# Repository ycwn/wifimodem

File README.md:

# wifimodem
ESP32 Wireless modem, compatible with PC XT/AT, C64, and Amiga

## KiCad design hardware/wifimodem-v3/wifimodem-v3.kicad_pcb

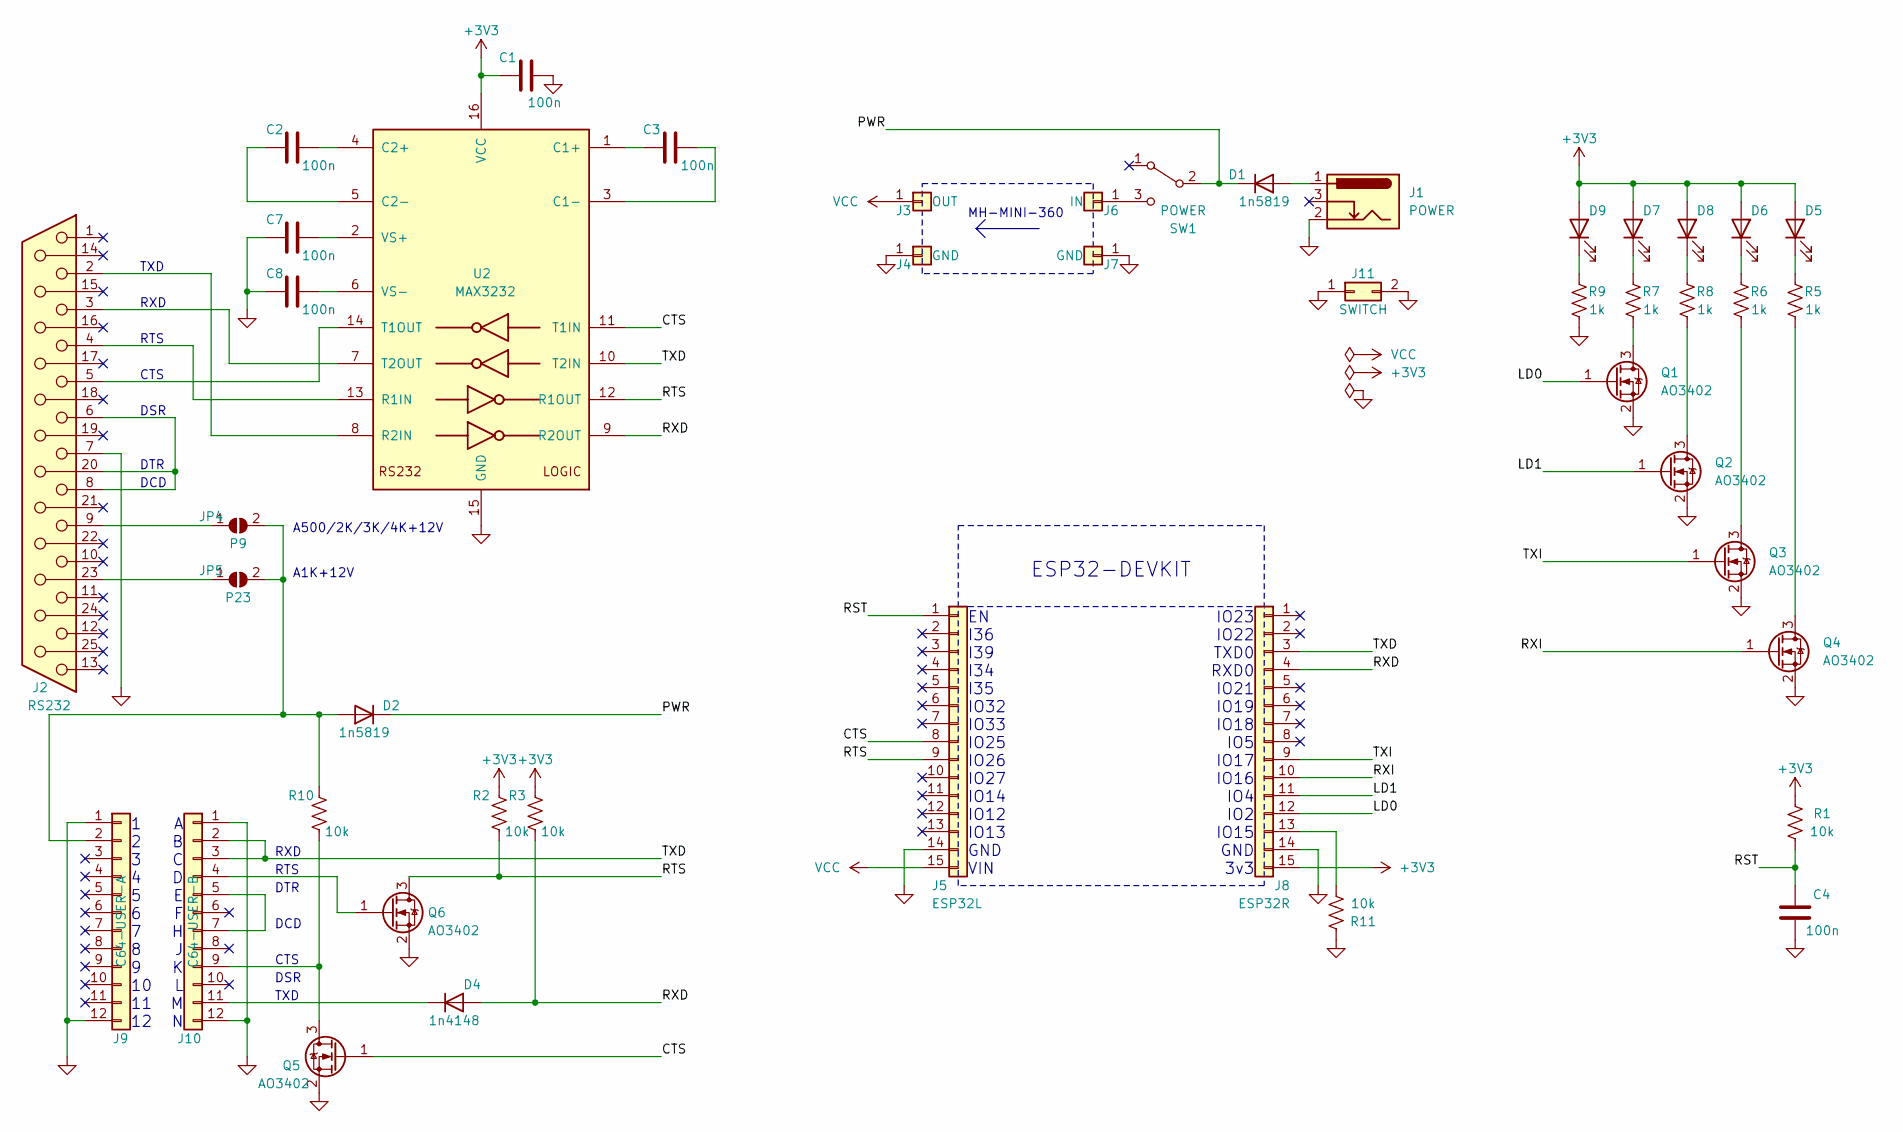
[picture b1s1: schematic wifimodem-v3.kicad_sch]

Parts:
C1, C2, C3, C4, C7, C8: 100n; C_0805_2012Metric
D1, D2: 1n5819; D_DO-34_SOD68_P2.54mm_Vertical_KathodeUp
D4: 1n4148; D_1206_3216Metric
D5: RXD; LED_D3.0mm
D6: TXD; LED_D3.0mm
D7: APS; LED_D3.0mm
D8: CON; LED_D3.0mm
D9: PWR; LED_D3.0mm
J1: POWER; BarrelJack_Horizontal
J2: RS232; DSUB-25_Female_Horizontal_P2.77x2.84mm_EdgePinOffset7.70mm_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
J3: OUT; TestPoint_Pad_2.0x2.0mm
J4, J7: GND; TestPoint_Pad_2.0x2.0mm
J5: ESP32L; PinSocket_1x15_P2.54mm_Vertical
J6: IN; TestPoint_Pad_2.0x2.0mm
J8: ESP32R; PinSocket_1x15_P2.54mm_Vertical
J9: C64-USER-A; Molex_KK-396_5273-12A_1x12_P3.96mm_Vertical
J10: C64-USER-B; Molex_KK-396_5273-12A_1x12_P3.96mm_Vertical
J11: SWITCH; PinSocket_2x01_P2.54mm_Horizontal
JP4: P9; SolderJumper-2_P1.3mm_Open_Pad1.0x1.5mm
JP5: P23; SolderJumper-2_P1.3mm_Open_Pad1.0x1.5mm
Q1, Q2, Q3, Q4, Q5, Q6: AO3402; SOT-23
R1, R2, R3, R10, R11: 10k; R_0805_2012Metric
R5, R6, R7, R8, R9: 1k; R_0805_2012Metric
SW1: POWER; PinSocket_1x03_P2.54mm_Vertical
U2: MAX3232; SOIC-16_3.9x9.9mm_P1.27mm

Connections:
+3V3: C1.1, D5.2 (A), D6.2 (A), D7.2 (A), D8.2 (A), D9.2 (A), J8.15, R1.2, R2.2, R3.2, U2.16 (VCC)
/CTS: J5.8, Q5.1 (G), U2.11 (T1IN)
/LD0: J8.12, Q1.1 (G)
/LD1: J8.11, Q2.1 (G)
/PWR: D1.1 (K), D2.1 (K), SW1.2 (B)
/RST: C4.1, J5.1, R1.1
/RTS: J5.9, Q6.3 (D), R2.1, U2.12 (R1OUT)
/RXD: D4.2 (A), J8.4, R3.1, U2.9 (R2OUT)
/RXI: J8.10, Q4.1 (G)
/TXD: J8.3, J10.2, J10.3, U2.10 (T2IN)
/TXI: J8.9, Q3.1 (G)
GND: C1.2, C4.2, C7.2, C8.2, J1.2, J2.7, J4.1, J5.14, J7.1, J8.14, J9.1, J9.12, J10.1, J10.12, J11.1, J11.2, Q1.2 (S), Q2.2 (S), Q3.2 (S), Q4.2 (S), Q5.2 (S), Q6.2 (S), R9.1, R11.2, U2.15 (GND)
unnamed: C2.1, U2.4 (C2+)
unnamed: C2.2, U2.5 (C2-)
unnamed: C3.1, U2.1 (C1+)
unnamed: C3.2, U2.3 (C1-)
unnamed: C7.1, U2.2 (VS+)
unnamed: C8.1, U2.6 (VS-)
unnamed: D1.2 (A), J1.1
unnamed: D2.2 (A), J9.2, JP4.2 (B), JP5.2 (B), R10.2
unnamed: D4.1 (K), J10.11
unnamed: D5.1 (K), R5.2
unnamed: D6.1 (K), R6.2
unnamed: D7.1 (K), R7.2
unnamed: D8.1 (K), R8.2
unnamed: D9.1 (K), R9.2
unnamed: J2.2, U2.8 (R2IN)
unnamed: J2.3, U2.7 (T2OUT)
unnamed: J2.4, U2.13 (R1IN)
unnamed: J2.5, U2.14 (T1OUT)
unnamed: J2.9, JP4.1 (A)
unnamed: J2.6, J2.8, J2.20
unnamed: J2.23, JP5.1 (A)
unnamed: J6.1, SW1.3 (C)
unnamed: J8.13, R11.1
unnamed: J10.4, Q6.1 (G)
unnamed: J10.5, J10.7
unnamed: J10.9, Q5.3 (D), R10.1
unnamed: Q1.3 (D), R7.1
unnamed: Q2.3 (D), R8.1
unnamed: Q3.3 (D), R6.1
unnamed: Q4.3 (D), R5.1
VCC: J3.1, J5.15

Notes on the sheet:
RTS
DTR
RXD
DCD
CTS
ESP32-DEVKIT
DSR
IO23 IO22 TXD0 RXD0 IO21 IO19 IO18 IO5 IO17 IO16 IO4 IO2 IO15 GND 3v3
A500/2K/3K/4K+12V
MH-MINI-360
A1K+12V
TXD
A B C D E F H J K L M N
1 2 3 4 5 6 7 8 9 10 11 12
EN I36 I39 I34 I35 IO32 IO33 IO25 IO26 IO27 IO14 IO12 IO13 GND VIN

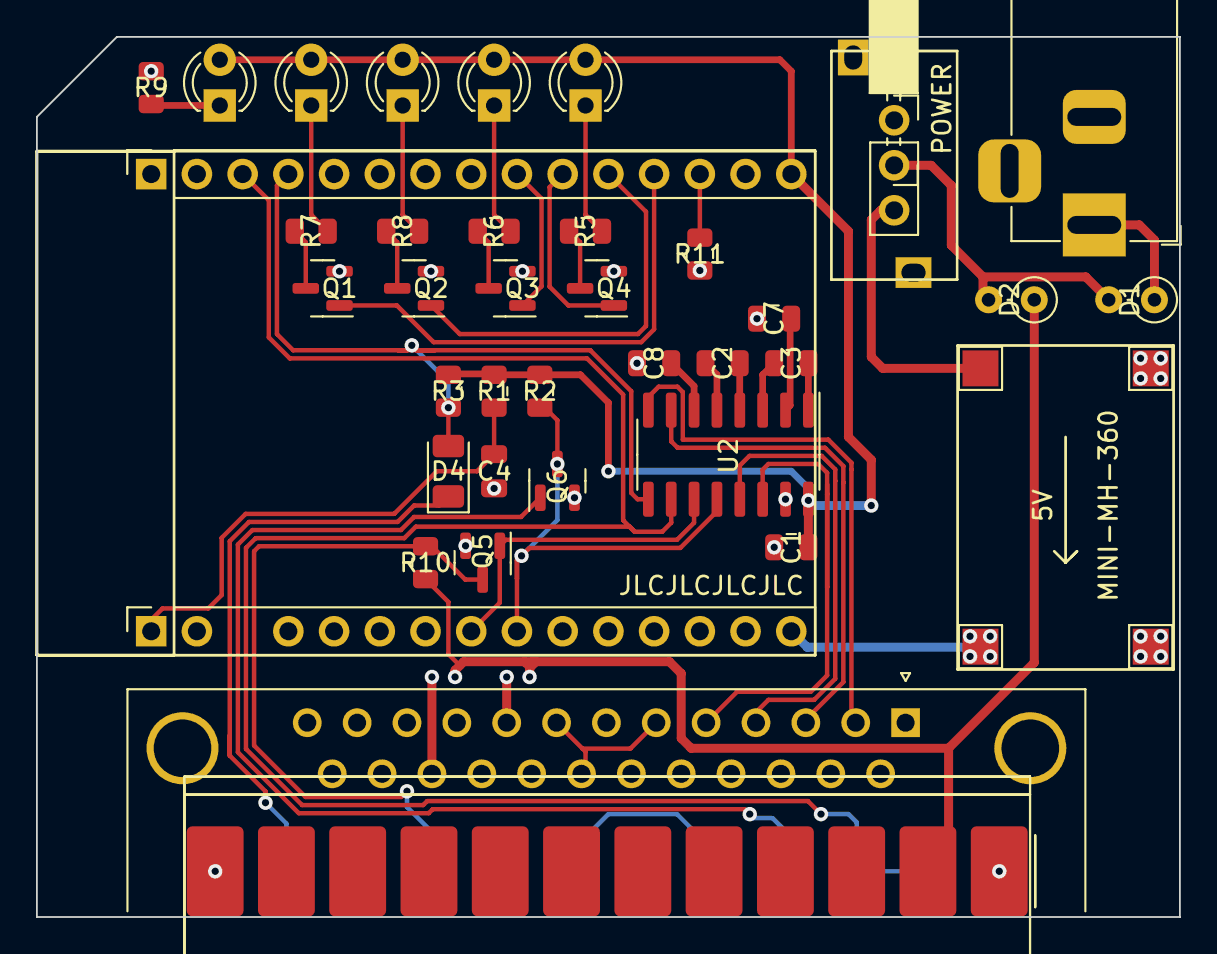
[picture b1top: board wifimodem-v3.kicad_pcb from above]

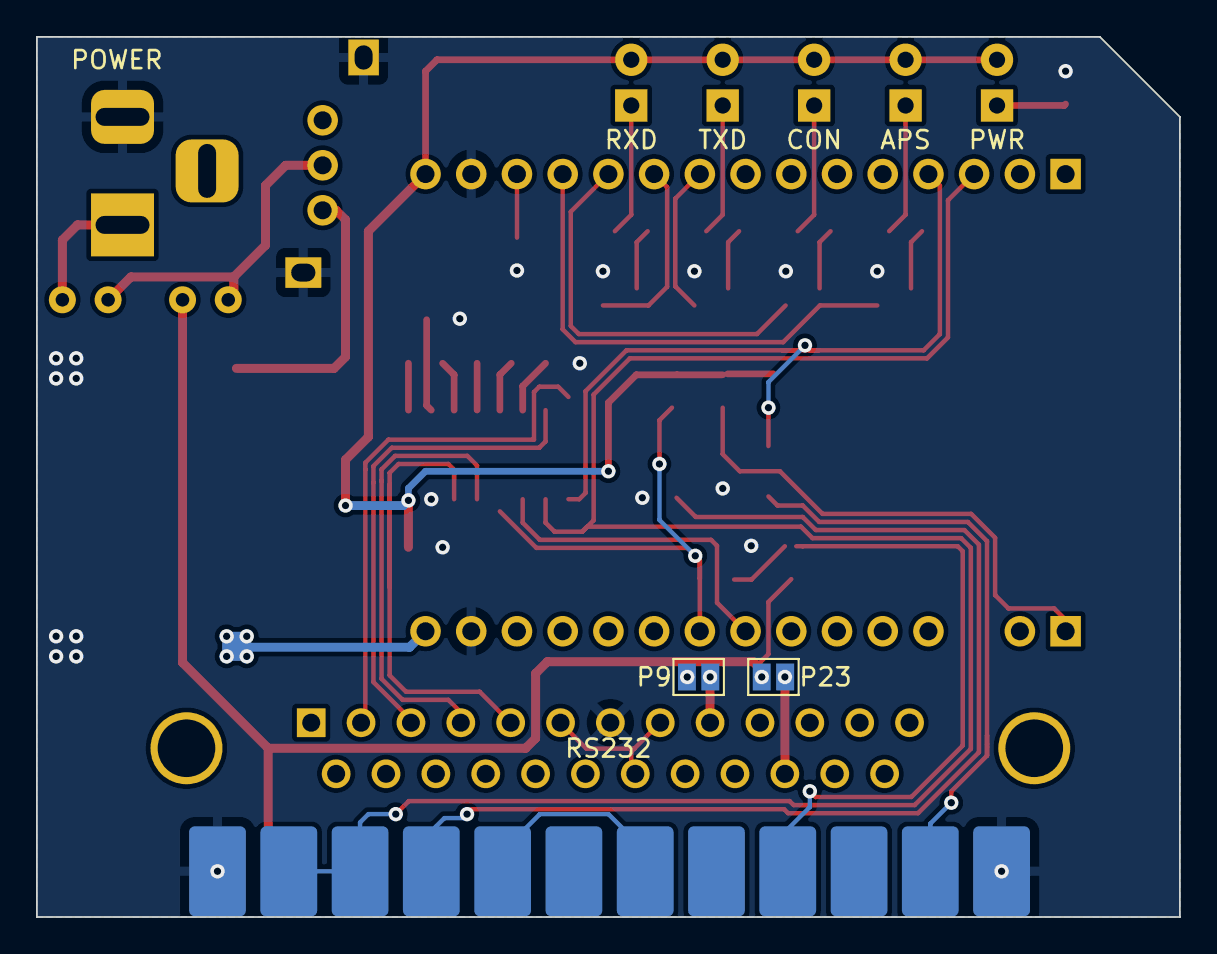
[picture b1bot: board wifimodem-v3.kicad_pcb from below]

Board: 2 copper layers, 63.5 x 48.9 mm, 45 parts (2 on the bottom side), 43 nets.

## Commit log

2026-05-13 ~ ESP-IDF project files ~ Introduced libraries: curl-8.13.0, libssh2-1.11.1, yxml ~ Build tools and helper scripts
2026-05-13 ~ Hardware design files, schematics and gerbers for JLCPCB
2026-05-13 ~ System core
2026-05-13 ~ Utility functions and various helpers
2026-05-17 ~ Serial port with automatic baudrate detector
2026-05-17 ~ Terminal control and I/O functionality
2026-05-17 ~ Wireless PHY implementation
2026-05-17 ~ LED status indicators and animation
